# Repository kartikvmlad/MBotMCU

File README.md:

# Astra Robotics Controller (ARC-2040)

**A high-performance embedded control board designed for autonomous mobile robotics.**

The **Astra Robotics Controller** bridges the gap between prototyping boards and industrial PLCs. Built around the Raspberry Pi **RP2040** microcontroller, it integrates high-current motor drivers, redundant sensing, and non-volatile "Black Box" data logging into a unified, vibration-resistant PCB.

-> To view the schematic, download the repository and open the file **MBot.kicad_sch** in KiCad 

---

## 📋 Table of Contents
- [System Architecture](#-system-architecture)
- [Technical Specifications](#-technical-specifications)
- [Pin Configuration](#-pin-configuration)
- [Power System & Safety](#-power-system--safety)
- [Fabrication Notes](#-fabrication-notes-bom-criticals)
- [Getting Started](#-getting-started)

---

## 🏗 System Architecture

The board is divided into four isolated subsystems to minimize noise and maximize reliability:

1.  **Core Logic:** RP2040 Dual-Core Cortex-M0+ running at 133MHz with 2MB QSPI Flash.
2.  **Actuation:** Dual **DRV8876** H-Bridge drivers capable of 5A peak current, featuring hardware current regulation and fault feedback.
3.  **Sensing:**
    * **Motion:** InvenSense **MPU-9150** (9-DoF IMU) for heading and stabilization.
    * **Environment:** Bosch **BMP280** for barometric altitude and temperature.
    * **Data Logging:** Cypress **FM24W256 F-RAM** for high-speed, infinite-endurance telemetry logging.
4.  **Power:** A hybrid 12V $\to$ 6.5V $\to$ 5V/3.3V power tree using a high-efficiency **XL4015** Buck Converter.

---

## ⚙ Technical Specifications

| Feature | Specification |
| :--- | :--- |
| **Microcontroller** | Raspberry Pi RP2040 (Dual Core ARM M0+ @ 133MHz) |
| **Input Voltage** | 10V - 14V DC (Optimized for 3S LiPo or 12V Lead Acid) |
| **Motor Drive Output** | 2x Channels, 6.5V Regulated @ 3A Continuous / 5A Peak |
| **Logic Voltage** | 3.3V (System) / 5.0V (Auxiliary) |
| **IMU** | MPU-9150 (Gyro + Accel + Mag) via I2C `0x68` |
| **Altimeter** | BMP280 via I2C `0x76` |
| **Non-Volatile Memory** | 256 Kbit (32KB) Ferroelectric RAM via I2C `0x50` |
| **Expansion** | 4x ADC, 2x UART, 1x I2C, 1x SPI |

---

## 📍 Pin Configuration

### External Interfaces
| Port Label | Function | Pinout | Voltage Level |
| :--- | :--- | :--- | :--- |
| **J1 (SWD)** | Firmware Debugging | SWDIO, SWCLK, GND | 3.3V |
| **J3 (ADC)** | Analog Sensors | ADC0-2, 3V3, AGND | 3.3V |
| **J7 (UART0)** | GPS / Lidar | TX, RX, 3V3, GND | 3.3V |
| **J8 (I2C)** | Expansion / OLED | SDA, SCL, 3V3, GND | 3.3V |
| **J14 (PWM)** | Servo / GPIO | PWM_A, PWM_B, 3V3, GND | 3.3V |

### Onboard Switch Multiplexer
The board features hardware toggle switches to route the RP2040 ADC lines:
* **Position A (Left):** ADC monitors **Motor Current** (via DRV8876 IPROPI).
* **Position B (Right):** ADC monitors **External Sensors** (via Port J3).

---

## ⚡ Power System & Safety

This board implements a **Split-Rail Architecture**:
* **VMOT (6.5V Rail):** Powered by an XL4015 Buck Converter. Dedicated to Motors and High-Torque Servos.
* **VSYS (5.0V Rail):** Powered by an AMS1117-5.0. Dedicated to logic-level conversion.
* **3V3 (Logic Rail):** Powered by onboard LDO for MCU and Sensors.

**Safety Features:**
* **Reverse Polarity Protection:** 5A Schottky Diodes on input.
* **Over-Current Protection:** On-board Fuse (F1) and software-readable Current Sense.
* **Thermal Protection:** DRV8876 drivers have automatic thermal shutdown with LED indication (`nFAULT`).

> **⚠️ Usage Warning:** Port `J8`, `J9`, and `J10` (Motor/Aux) supply **6.5V** on Pin 3. Do not connect standard 5V-intolerant logic devices to this pin without checking datasheets.

---

## 🛠 Fabrication Notes (BOM Criticals)

If fabricating this board from the provided Gerbers, strictly adhere to the following component requirements to ensure power stability:

1.  **Diodes (D4, D5, D6):** MUST be **SS54** (5 Amp) or **MBRD1045** (10 Amp). Using SS34 (3A) may result in thermal failure under load.
2.  **Inductor (L1):** Footprint requires a **Shielded Power Inductor** (e.g., CDRH127) rated for **Isat > 5A**.
3.  **Capacitors:**
    * **Cout1:** 330µF/25V Electrolytic Low-ESR is mandatory for 6.5V rail stability.

---

## 🚀 Getting Started

1.  **Hardware Setup:**
    * Connect a 12V battery to the Screw Terminal (J3) or Barrel Jack (J2).
    * Connect motors to the JST outputs `M0` and `M1`.
2.  **Firmware Upload:**
    * Hold the **BOOT** button (or short `BOOTSEL` jumper).
    * Connect USB-C to a PC.
    * Copy your `.uf2` file to the `RPI-RP2` drive.
3.  **Software Addresses:**
    * `BMP280`: **0x76**
    * `MPU9150`: **0x68**
    * `FRAM`: **0x50**

---

**Project Lead:** Kartik Lad  
**Organization:** Astra Robotics  
**License:** Open Source Hardware

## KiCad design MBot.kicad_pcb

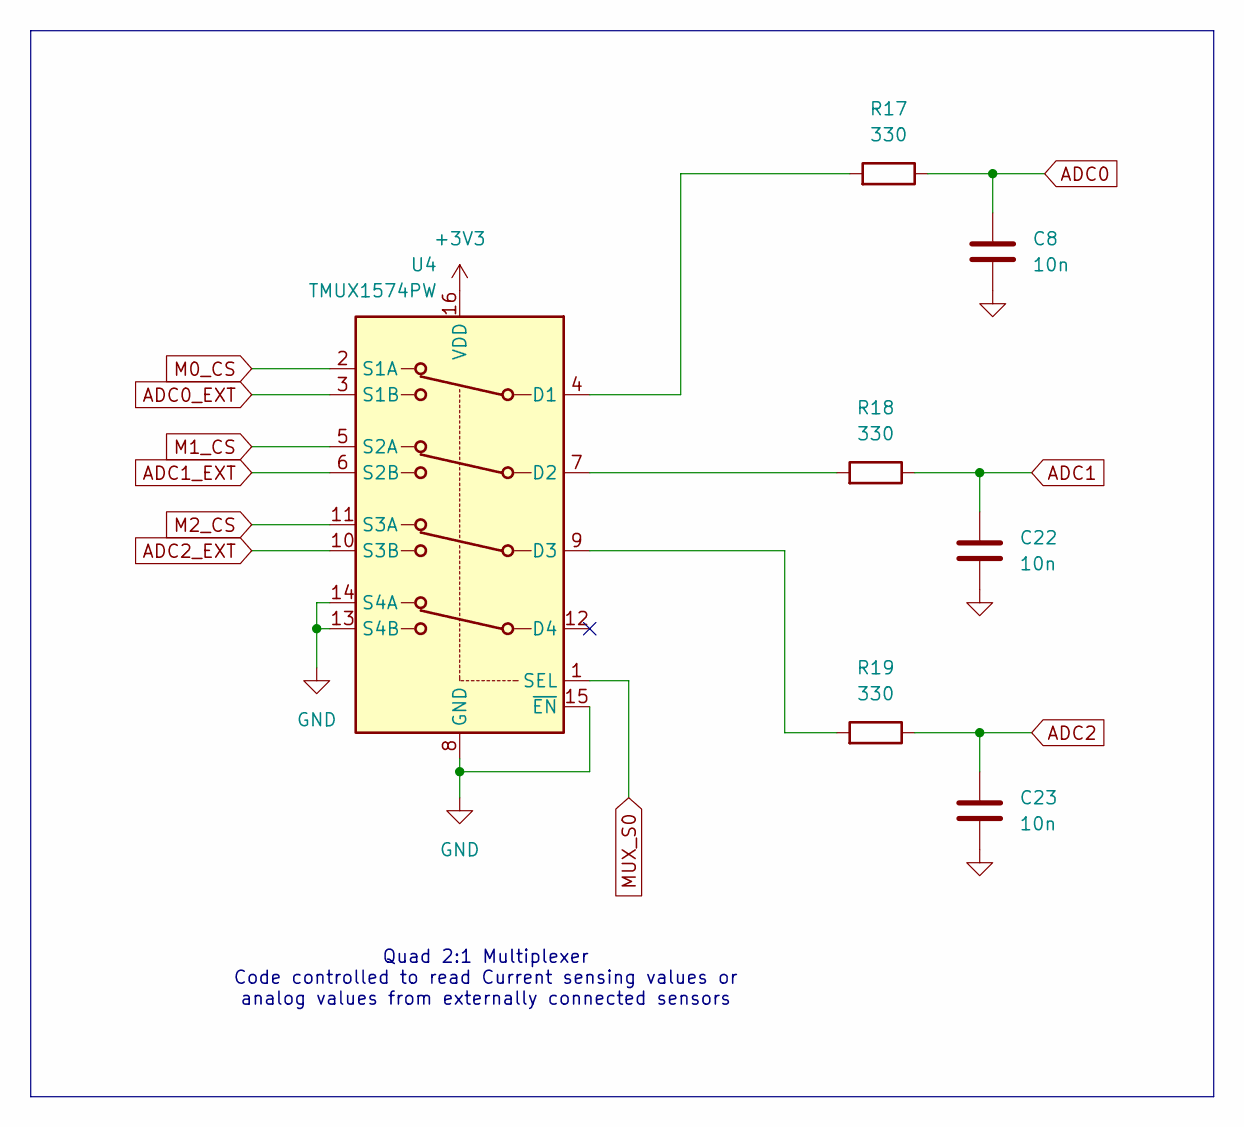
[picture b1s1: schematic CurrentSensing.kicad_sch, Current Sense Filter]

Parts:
C8, C22, C23: 10n; C_0603_1608Metric_Pad1.08x0.95mm_HandSolder
R17, R18, R19: 330; R_0603_1608Metric_Pad0.98x0.95mm_HandSolder
U4: TMUX1574PW; TSSOP-16_4.4x5mm_P0.65mm

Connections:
+3V3: U4.16 (VDD); also elsewhere on the board
ADC0: C8.1, R17.1; also elsewhere on the board
ADC0_EXT: U4.3 (S1B); also elsewhere on the board
ADC1: C22.1, R18.1; also elsewhere on the board
ADC1_EXT: U4.6 (S2B); also elsewhere on the board
ADC2: C23.1, R19.1; also elsewhere on the board
ADC2_EXT: U4.10 (S3B); also elsewhere on the board
GND: C8.2, C22.2, C23.2, U4.8 (GND), U4.13 (S4B), U4.14 (S4A), U4.15 (~EN); also elsewhere on the board
M0_CS: U4.2 (S1A); also elsewhere on the board
M1_CS: U4.5 (S2A); also elsewhere on the board
M2_CS: U4.11 (S3A); also elsewhere on the board
MUX_S0: U4.1 (SEL); also elsewhere on the board
unnamed: R17.2, U4.4 (D1)
unnamed: R18.2, U4.7 (D2)
unnamed: R19.2, U4.9 (D3)

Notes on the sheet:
Quad 2:1 Multiplexer Code controlled to read Current sensing values or analog values from externally connected sensors

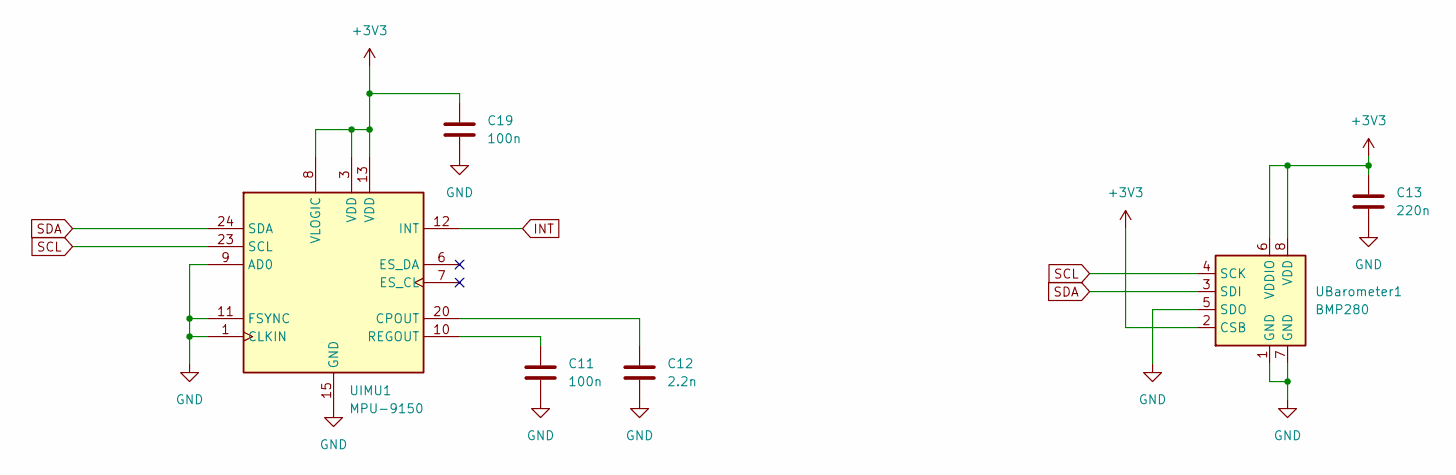
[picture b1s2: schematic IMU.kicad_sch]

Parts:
C11, C19: 100n; C_0603_1608Metric_Pad1.08x0.95mm_HandSolder
C12: 2.2n; C_0603_1608Metric_Pad1.08x0.95mm_HandSolder
C13: 220n; C_0603_1608Metric_Pad1.08x0.95mm_HandSolder
UBarometer1: BMP280; Bosch_LGA-8_2x2.5mm_P0.65mm_ClockwisePinNumbering
UIMU1: MPU-9150; InvenSense_QFN-24_4x4mm_P0.5mm

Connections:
+3V3: C13.1, C19.1, UBarometer1.2 (CSB), UBarometer1.6 (VDDIO), UBarometer1.8 (VDD), UIMU1.3 (VDD), UIMU1.8 (VLOGIC), UIMU1.13 (VDD); also elsewhere on the board
GND: C11.2, C12.2, C13.2, C19.2, UBarometer1.1 (GND), UBarometer1.5 (SDO), UBarometer1.7 (GND), UIMU1.1 (CLKIN), UIMU1.9 (AD0), UIMU1.11 (FSYNC), UIMU1.15 (GND), UIMU1.17 (GND), UIMU1.18 (GND); also elsewhere on the board
INT: UIMU1.12 (INT); also elsewhere on the board
unnamed: C12.1, UIMU1.20 (CPOUT)
unnamed: C11.1, UIMU1.10 (REGOUT)
SCL: UBarometer1.4 (SCK), UIMU1.23 (SCL); also elsewhere on the board
SDA: UBarometer1.3 (SDI), UIMU1.24 (SDA); also elsewhere on the board

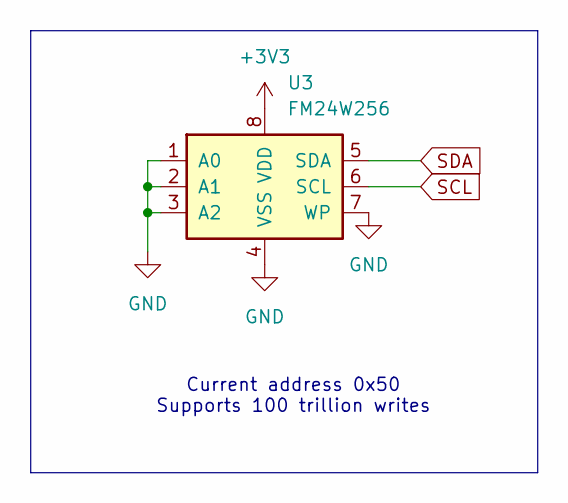
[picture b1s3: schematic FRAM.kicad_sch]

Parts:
U3: FM24W256; SOIC-8_3.9x4.9mm_P1.27mm

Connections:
+3V3: U3.8 (VDD); also elsewhere on the board
GND: U3.1 (A0), U3.2 (A1), U3.3 (A2), U3.4 (VSS), U3.7 (WP); also elsewhere on the board
SCL: U3.6 (SCL); also elsewhere on the board
SDA: U3.5 (SDA); also elsewhere on the board

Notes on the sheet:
Current address 0x50 Supports 100 trillion writes

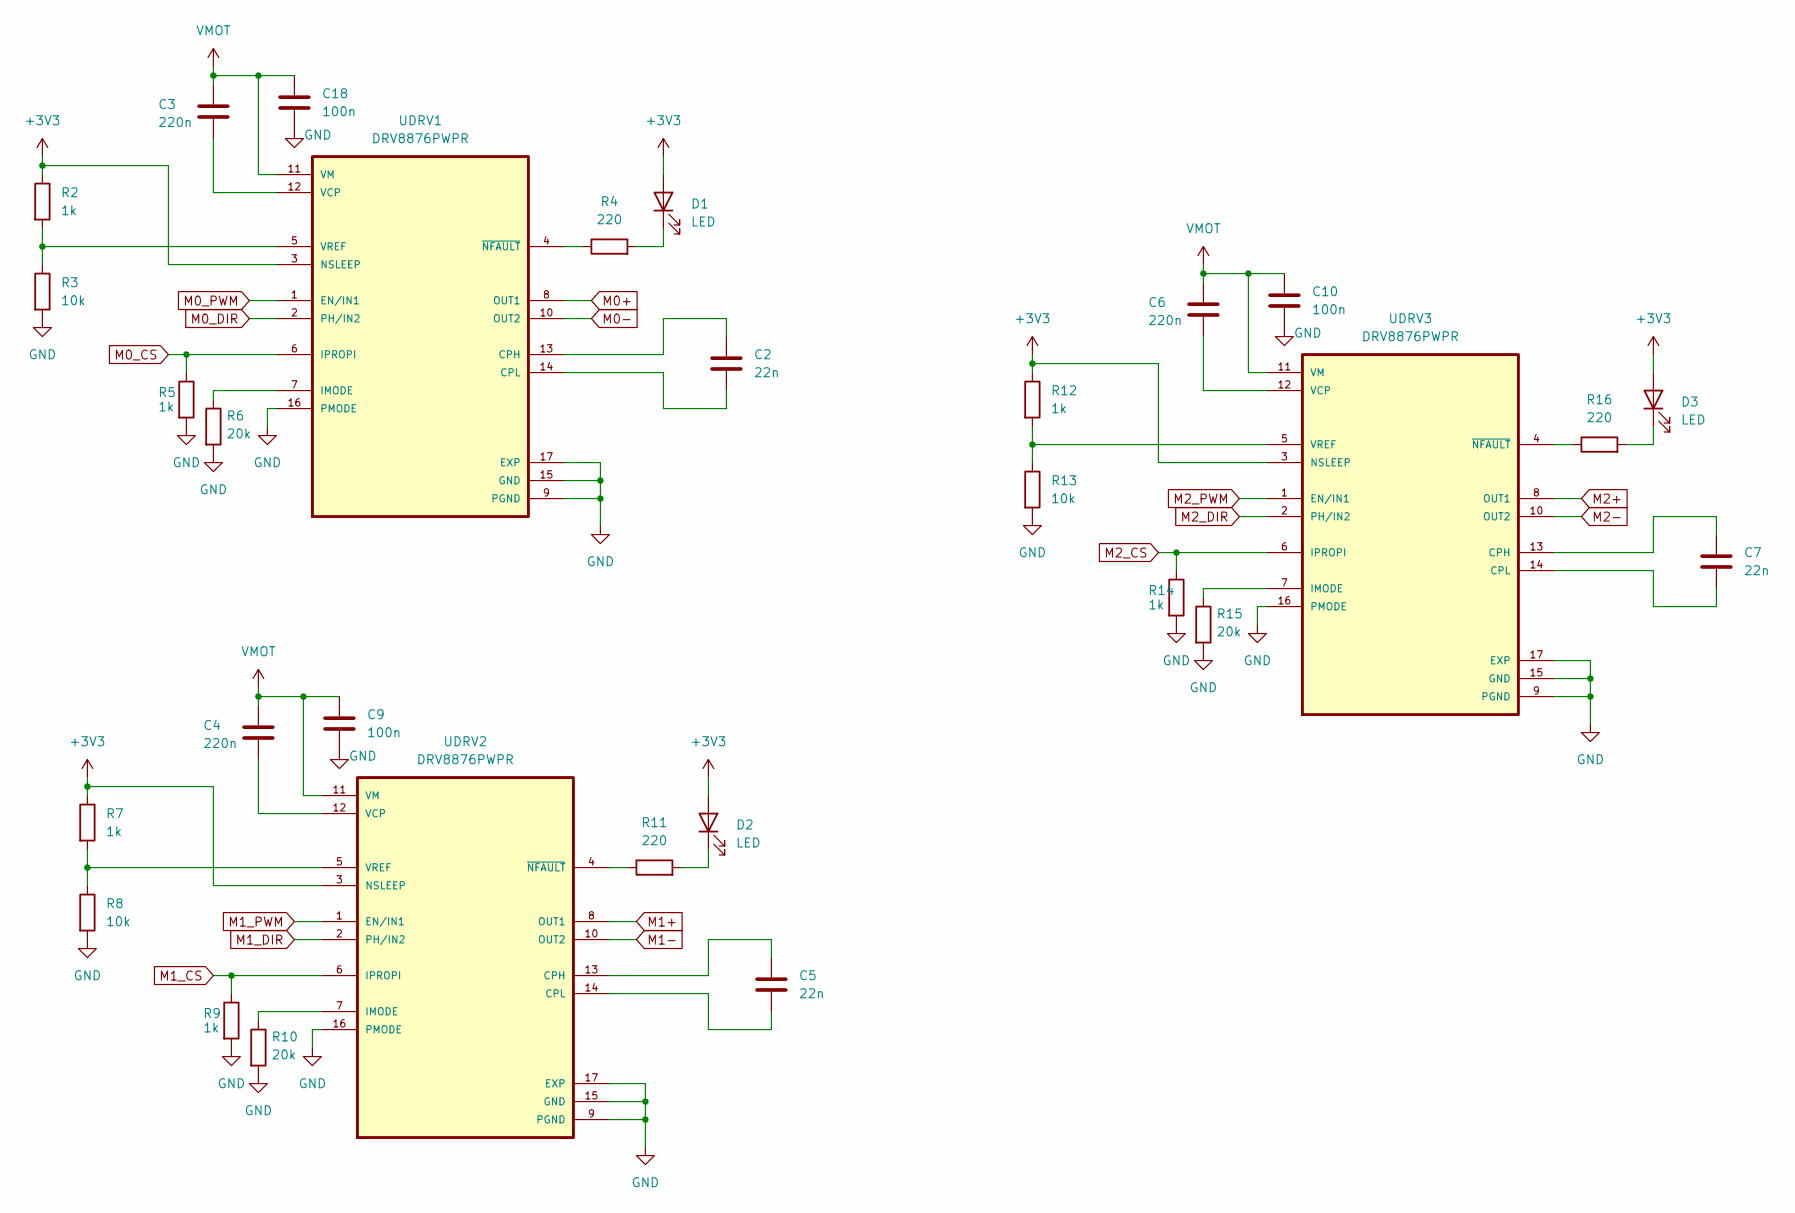
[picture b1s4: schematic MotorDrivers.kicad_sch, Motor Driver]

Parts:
C2, C5, C7: 22n; C_0603_1608Metric_Pad1.08x0.95mm_HandSolder
C3, C4, C6: 220n; C_0603_1608Metric_Pad1.08x0.95mm_HandSolder
C9, C10, C18: 100n; C_0603_1608Metric_Pad1.08x0.95mm_HandSolder
D1, D2, D3: LED; LED_0805_2012Metric_Pad1.15x1.40mm_HandSolder
R2, R5, R7, R9, R12, R14: 1k; R_0603_1608Metric_Pad0.98x0.95mm_HandSolder
R3, R8, R13: 10k; R_0603_1608Metric_Pad0.98x0.95mm_HandSolder
R4, R11, R16: 220; R_0603_1608Metric_Pad0.98x0.95mm_HandSolder
R6, R10, R15: 20k; R_0603_1608Metric_Pad0.98x0.95mm_HandSolder
UDRV1, UDRV2, UDRV3: DRV8876PWPR; IC_DRV8876PWPR; PARTREV E

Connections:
+3V3: D1.2 (A), D2.2 (A), D3.2 (A), R2.1, R7.1, R12.1, UDRV1.3 (NSLEEP), UDRV2.3 (NSLEEP), UDRV3.3 (NSLEEP); also elsewhere on the board
GND: C9.2, C10.2, C18.2, R3.2, R5.2, R6.2, R8.2, R9.2, R10.2, R13.2, R14.2, R15.2, UDRV1.9 (PGND), UDRV1.15 (GND), UDRV1.16 (PMODE), UDRV1.17 (EXP), UDRV2.9 (PGND), UDRV2.15 (GND), UDRV2.16 (PMODE), UDRV2.17 (EXP), UDRV3.9 (PGND), UDRV3.15 (GND), UDRV3.16 (PMODE), UDRV3.17 (EXP); also elsewhere on the board
M0+: UDRV1.8 (OUT1); also elsewhere on the board
M0-: UDRV1.10 (OUT2); also elsewhere on the board
M0_CS: R5.1, UDRV1.6 (IPROPI); also elsewhere on the board
M0_DIR: UDRV1.2 (PH/IN2); also elsewhere on the board
M0_PWM: UDRV1.1 (EN/IN1); also elsewhere on the board
M1+: UDRV2.8 (OUT1); also elsewhere on the board
M1-: UDRV2.10 (OUT2); also elsewhere on the board
M1_CS: R9.1, UDRV2.6 (IPROPI); also elsewhere on the board
M1_DIR: UDRV2.2 (PH/IN2); also elsewhere on the board
M1_PWM: UDRV2.1 (EN/IN1); also elsewhere on the board
M2+: UDRV3.8 (OUT1); also elsewhere on the board
M2-: UDRV3.10 (OUT2); also elsewhere on the board
M2_CS: R14.1, UDRV3.6 (IPROPI); also elsewhere on the board
M2_DIR: UDRV3.2 (PH/IN2); also elsewhere on the board
M2_PWM: UDRV3.1 (EN/IN1); also elsewhere on the board
unnamed: D1.1 (K), R4.2
unnamed: D2.1 (K), R11.2
unnamed: D3.1 (K), R16.2
unnamed: C2.1, UDRV1.13 (CPH)
unnamed: C2.2, UDRV1.14 (CPL)
unnamed: R6.1, UDRV1.7 (IMODE)
unnamed: C3.2, UDRV1.12 (VCP)
unnamed: R2.2, R3.1, UDRV1.5 (VREF)
unnamed: R4.1, UDRV1.4 (~NFAULT)
unnamed: C5.1, UDRV2.13 (CPH)
unnamed: C5.2, UDRV2.14 (CPL)
unnamed: R10.1, UDRV2.7 (IMODE)
unnamed: C4.2, UDRV2.12 (VCP)
unnamed: R7.2, R8.1, UDRV2.5 (VREF)
unnamed: R11.1, UDRV2.4 (~NFAULT)
unnamed: C7.1, UDRV3.13 (CPH)
unnamed: C7.2, UDRV3.14 (CPL)
unnamed: R15.1, UDRV3.7 (IMODE)
unnamed: C6.2, UDRV3.12 (VCP)
unnamed: R12.2, R13.1, UDRV3.5 (VREF)
unnamed: R16.1, UDRV3.4 (~NFAULT)
VMOT: C3.1, C4.1, C6.1, C9.1, C10.1, C18.1, UDRV1.11 (VM), UDRV2.11 (VM), UDRV3.11 (VM); also elsewhere on the board

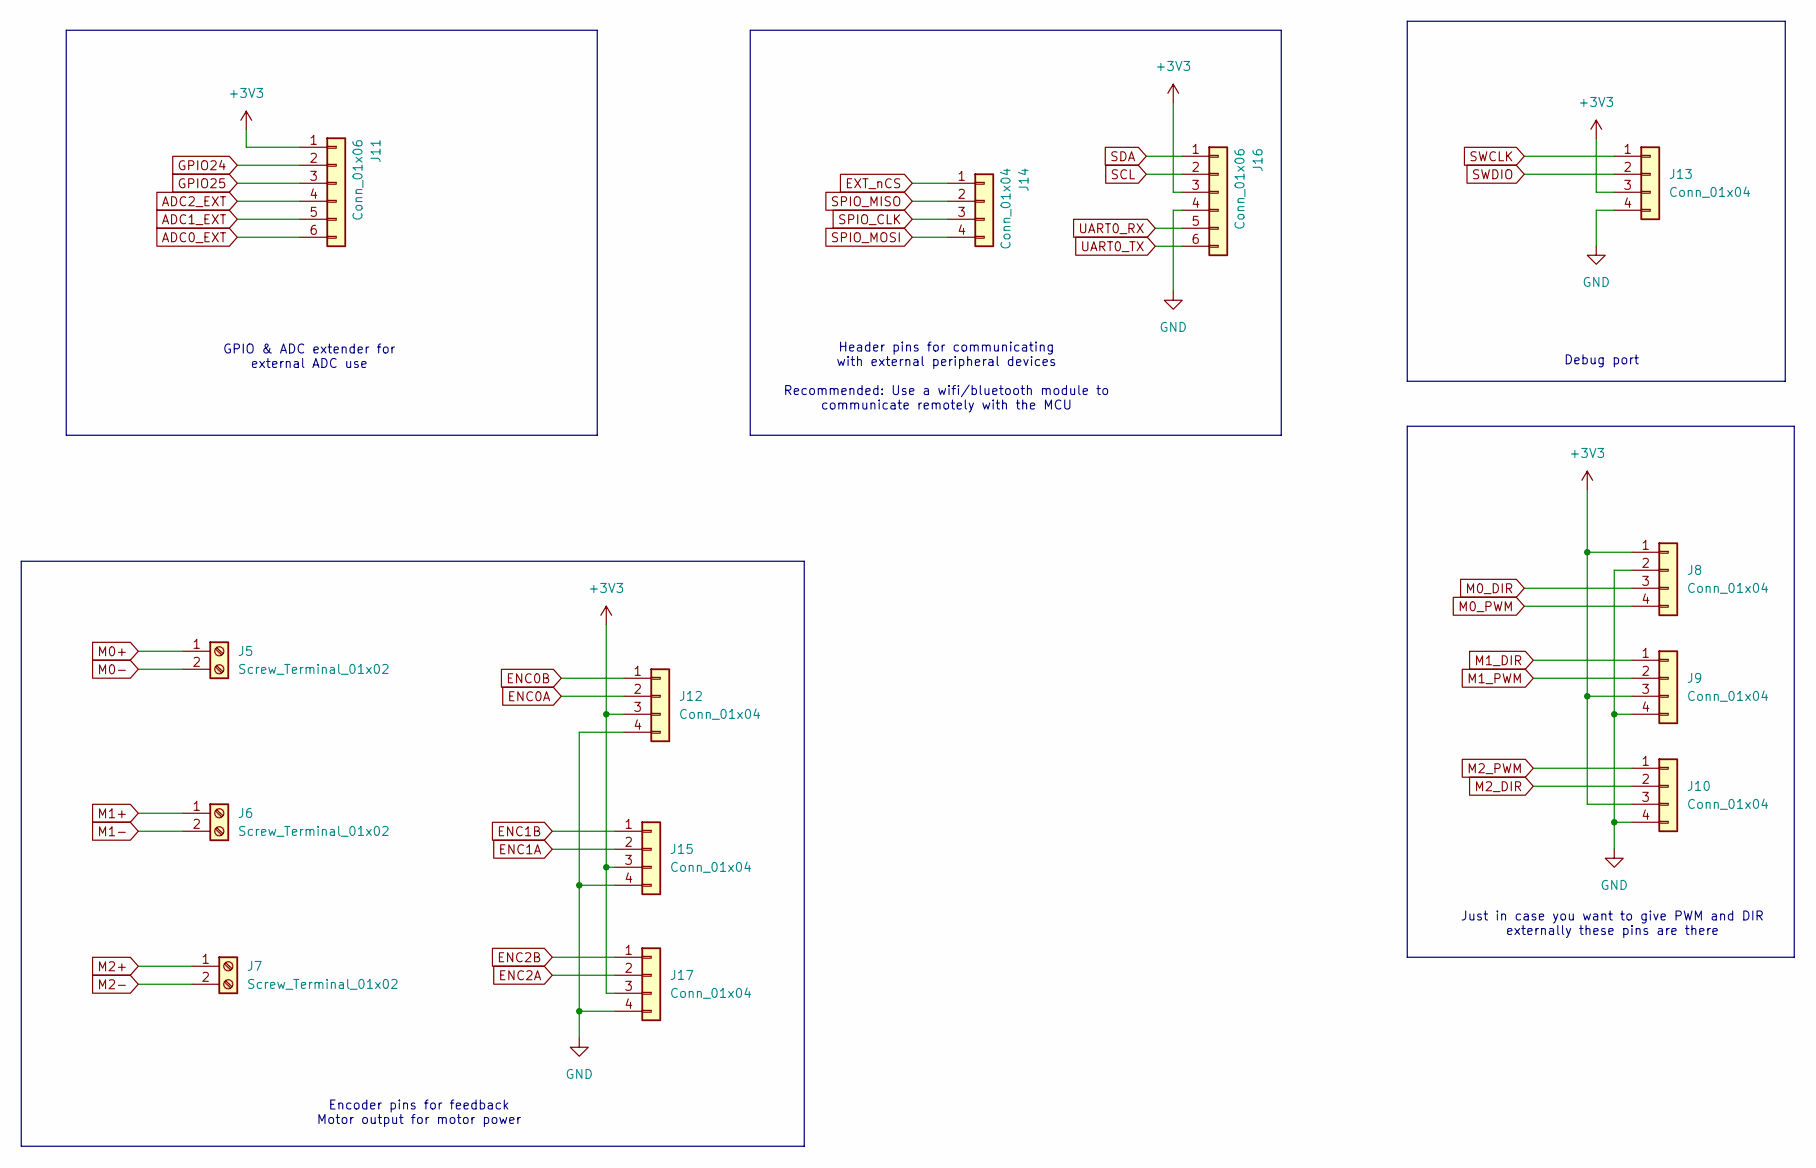
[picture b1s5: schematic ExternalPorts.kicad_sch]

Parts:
J5, J6, J7: Screw_Terminal_01x02; TerminalBlock_Phoenix_MPT-0,5-2-2.54_1x02_P2.54mm_Horizontal
J8, J9, J10, J12, J13, J14, J15, J17: Conn_01x04; JST_ZH_B4B-ZR_1x04_P1.50mm_Vertical
J11, J16: Conn_01x06; JST_ZH_B6B-ZR_1x06_P1.50mm_Vertical

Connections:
+3V3: J8.1, J9.3, J10.3, J11.1, J12.3, J13.3, J15.3, J16.3, J17.3; also elsewhere on the board
ADC0_EXT: J11.6; also elsewhere on the board
ADC1_EXT: J11.5; also elsewhere on the board
ADC2_EXT: J11.4; also elsewhere on the board
ENC0A: J12.2; also elsewhere on the board
ENC0B: J12.1; also elsewhere on the board
ENC1A: J15.2; also elsewhere on the board
ENC1B: J15.1; also elsewhere on the board
ENC2A: J17.2; also elsewhere on the board
ENC2B: J17.1; also elsewhere on the board
EXT_nCS: J14.1; also elsewhere on the board
GND: J8.2, J9.4, J10.4, J12.4, J13.4, J15.4, J16.4, J17.4; also elsewhere on the board
GPIO24: J11.2; also elsewhere on the board
GPIO25: J11.3; also elsewhere on the board
M0+: J5.1; also elsewhere on the board
M0-: J5.2; also elsewhere on the board
M0_DIR: J8.3; also elsewhere on the board
M0_PWM: J8.4; also elsewhere on the board
M1+: J6.1; also elsewhere on the board
M1-: J6.2; also elsewhere on the board
M1_DIR: J9.1; also elsewhere on the board
M1_PWM: J9.2; also elsewhere on the board
M2+: J7.1; also elsewhere on the board
M2-: J7.2; also elsewhere on the board
M2_DIR: J10.2; also elsewhere on the board
M2_PWM: J10.1; also elsewhere on the board
SCL: J16.2; also elsewhere on the board
SDA: J16.1; also elsewhere on the board
SPIO_CLK: J14.3; also elsewhere on the board
SPIO_MISO: J14.2; also elsewhere on the board
SPIO_MOSI: J14.4; also elsewhere on the board
SWCLK: J13.1; also elsewhere on the board
SWDIO: J13.2; also elsewhere on the board
UART0_RX: J16.5; also elsewhere on the board
UART0_TX: J16.6; also elsewhere on the board

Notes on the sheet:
GPIO & ADC extender for external ADC use
Debug port
Just in case you want to give PWM and DIR externally these pins are there
Header pins for communicating with external peripheral devices Recommended: Use a wifi/bluetooth module to communicate remotely with the MCU
Encoder pins for feedback Motor output for motor power

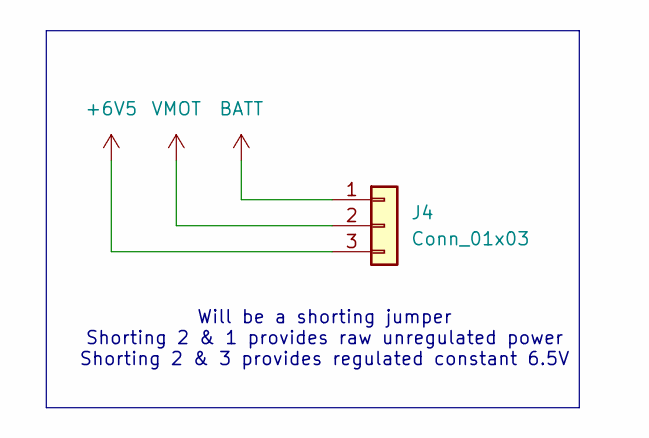
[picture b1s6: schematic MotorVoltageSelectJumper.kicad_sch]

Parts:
J4: Conn_01x03; JST_VH_B3P-VH_1x03_P3.96mm_Vertical

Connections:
+6V5: J4.3; also elsewhere on the board
BATT: J4.1; also elsewhere on the board
VMOT: J4.2; also elsewhere on the board

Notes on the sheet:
Will be a shorting jumper Shorting 2 & 1 provides raw unregulated power Shorting 2 & 3 provides regulated constant 6.5V

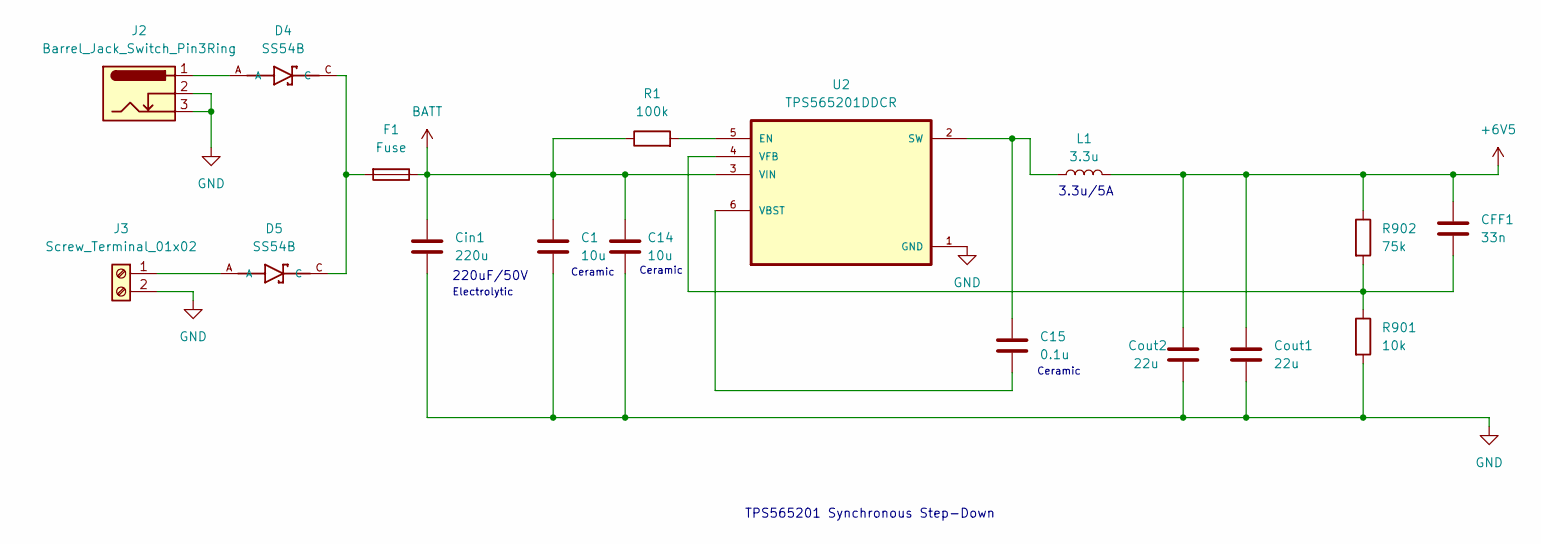
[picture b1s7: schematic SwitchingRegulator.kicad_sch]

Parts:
C1, C14: 10u; C_0805_2012Metric_Pad1.18x1.45mm_HandSolder
C15: 0.1u; C_0603_1608Metric_Pad1.08x0.95mm_HandSolder
CFF1: 33n; C_0603_1608Metric_Pad1.08x0.95mm_HandSolder
Cin1: 220u; C_0805_2012Metric_Pad1.18x1.45mm_HandSolder
Cout1, Cout2: 22u; C_0805_2012Metric_Pad1.18x1.45mm_HandSolder
D4, D5: SS54B; DIOM4336X244N
F1: Fuse; Fuse_Littelfuse-NANO2-451_453
J2: Barrel_Jack_Switch_Pin3Ring; BarrelJack_Horizontal
J3: Screw_Terminal_01x02; TerminalBlock_Phoenix_MPT-0,5-2-2.54_1x02_P2.54mm_Horizontal
L1: 3.3u; L_Bourns_SRP7028A_7.3x6.6mm
R1: 100k; R_0603_1608Metric_Pad0.98x0.95mm_HandSolder
R901: 10k; R_0603_1608Metric_Pad0.98x0.95mm_HandSolder
R902: 75k; R_0603_1608Metric_Pad0.98x0.95mm_HandSolder
U2: TPS565201DDCR; SOT95P280X110-6N

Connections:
+6V5: CFF1.1, Cout1.1, Cout2.1, L1.2, R902.1; also elsewhere on the board
BATT: C1.1, C14.1, Cin1.1, F1.1, R1.1, U2.3 (VIN); also elsewhere on the board
GND: C1.2, C14.2, Cin1.2, Cout1.2, Cout2.2, J2.2, J2.3, J3.2, R901.2, U2.1 (GND); also elsewhere on the board
unnamed: D4.A, J2.1
unnamed: D4.C, D5.C, F1.2
unnamed: D5.A, J3.1
unnamed: R1.2, U2.5 (EN)
unnamed: C15.1, L1.1, U2.2 (SW)
unnamed: C15.2, U2.6 (VBST)
unnamed: CFF1.2, R901.1, R902.2, U2.4 (VFB)

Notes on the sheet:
Ceramic
TPS565201 Synchronous Step-Down
220uF/50V
Electrolytic
3.3u/5A

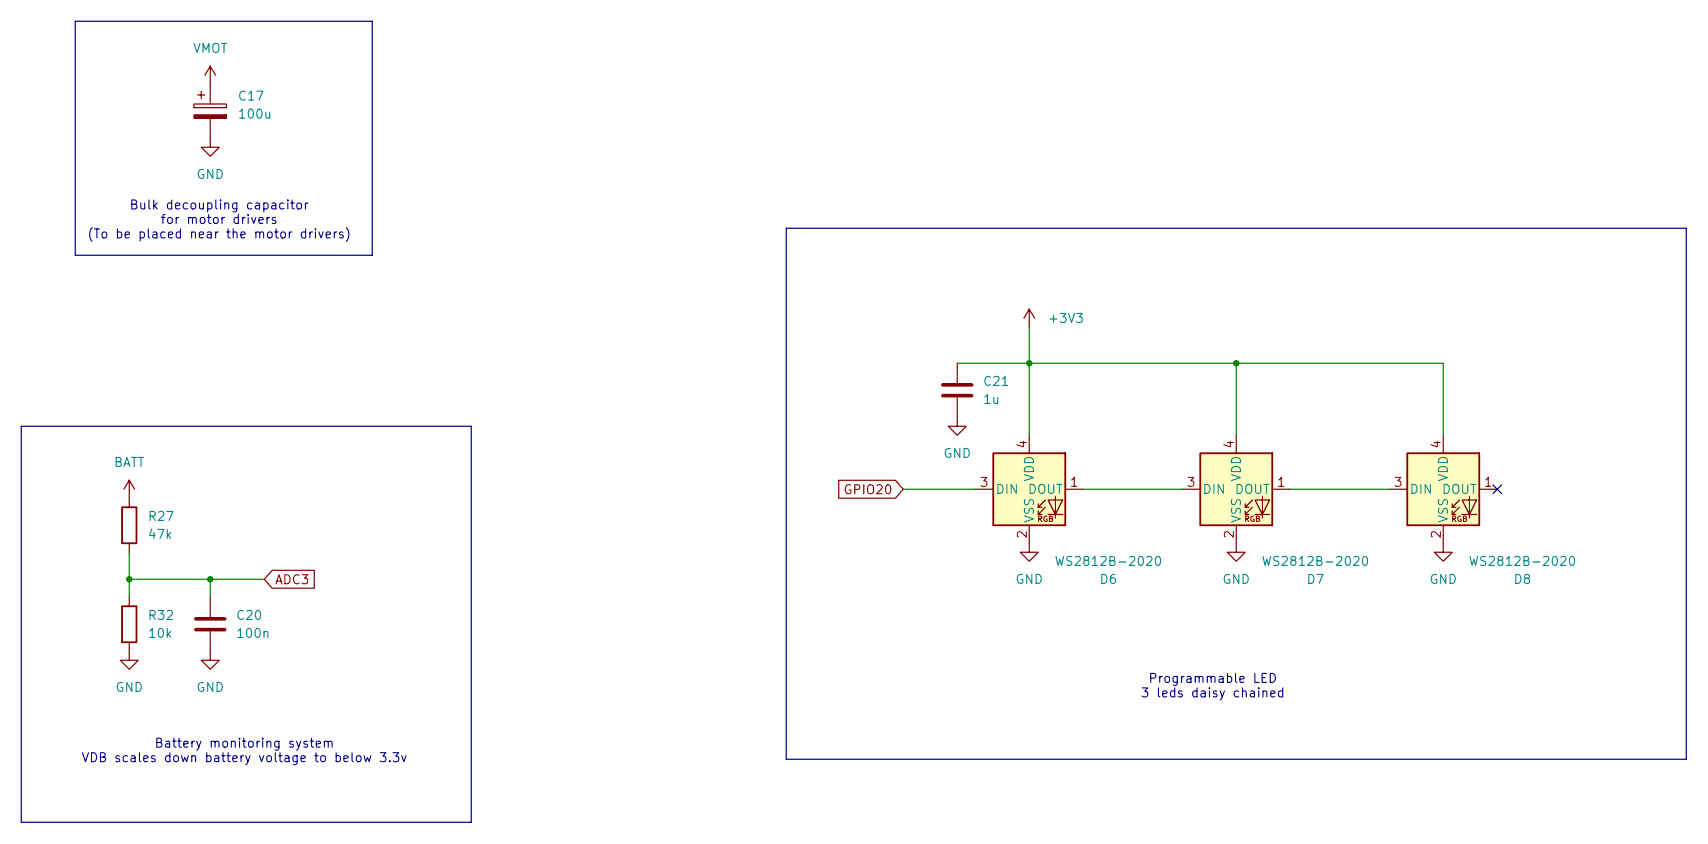
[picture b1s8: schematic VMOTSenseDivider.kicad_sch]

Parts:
C17: 100u; C_0805_2012Metric_Pad1.18x1.45mm_HandSolder
C20: 100n; C_0603_1608Metric_Pad1.08x0.95mm_HandSolder
C21: 1u; C_0603_1608Metric_Pad1.08x0.95mm_HandSolder
D6, D7, D8: WS2812B-2020; LED_WS2812B-2020_PLCC4_2.0x2.0mm
R27: 47k; R_0603_1608Metric_Pad0.98x0.95mm_HandSolder
R32: 10k; R_0603_1608Metric_Pad0.98x0.95mm_HandSolder

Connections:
+3V3: C21.1, D6.4 (VDD), D7.4 (VDD), D8.4 (VDD); also elsewhere on the board
ADC3: C20.1, R27.2, R32.1; also elsewhere on the board
BATT: R27.1; also elsewhere on the board
GND: C17.2, C20.2, C21.2, D6.2 (VSS), D7.2 (VSS), D8.2 (VSS), R32.2; also elsewhere on the board
GPIO20: D6.3 (DIN); also elsewhere on the board
unnamed: D6.1 (DOUT), D7.3 (DIN)
unnamed: D7.1 (DOUT), D8.3 (DIN)
VMOT: C17.1; also elsewhere on the board

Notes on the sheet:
Battery monitoring system VDB scales down battery voltage to below 3.3v
Bulk decoupling capacitor for motor drivers (To be placed near the motor drivers)
Programmable LED 3 leds daisy chained

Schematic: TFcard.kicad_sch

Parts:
J1: Micro_SD_Card_Det1; microSD_HC_Hirose_DM3AT-SF-PEJM5
U1: 74AUC1G19; SOT-23-6_Handsoldering

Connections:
+3V3: J1.4 (VDD), U1.5 (VCC); also elsewhere on the board
EXT_nCS: U1.6 (Y0); also elsewhere on the board
EXT/SD: U1.1 (A); also elsewhere on the board
GND: J1.6 (VSS), J1.10 (SHIELD), U1.2 (GND); also elsewhere on the board
SD_nCS: J1.2 (DAT3/CD), U1.4 (Y1)
SPIO_CLK: J1.5 (CLK); also elsewhere on the board
SPIO_CS: U1.3 (~E); also elsewhere on the board
SPIO_MISO: J1.7 (DAT0); also elsewhere on the board
SPIO_MOSI: J1.3 (CMD); also elsewhere on the board

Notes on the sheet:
DET is for physical detection of card

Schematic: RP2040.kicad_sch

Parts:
C16, C105, C106, C107, C109, C110, C111, C112, C113, C114, C115, C120: 100n; C_0603_1608Metric_Pad1.08x0.95mm_HandSolder
C101, C104, C117: 10u; C_0805_2012Metric_Pad1.18x1.45mm_HandSolder
C102, C103: 15p; C_0603_1608Metric_Pad1.08x0.95mm_HandSolder
C108: 1u; C_0603_1608Metric_Pad1.08x0.95mm_HandSolder
D101, D102: SS14; D_SMA_Handsoldering
FB1: FerriteBead; L_0805_2012Metric_Pad1.05x1.20mm_HandSolder
JUSBC1: USB_C_Receptacle_USB2.0_16P; USB_C_Receptacle_GCT_USB4085
R23, R24: 4.7k; R_0603_1608Metric_Pad0.98x0.95mm_HandSolder
R101, R105: 1k; R_0603_1608Metric_Pad0.98x0.95mm_HandSolder
R109: 5.1k; R_0603_1608Metric_Pad0.98x0.95mm_HandSolder
RDminus1: 27; R_0603_1608Metric_Pad0.98x0.95mm_HandSolder
RDplus1: 27; R_0603_1608Metric_Pad0.98x0.95mm_HandSolder
RUSB1: 5.1k; R_0603_1608Metric_Pad0.98x0.95mm_HandSolder
SW4: SW_SPST; SW_Push_SPST_NO_Alps_SKRK
SWRESET1: SW_SPST; SW_Push_SPST_NO_Alps_SKRK
UESD1: USBLC6-2SC6; SOT-23-6
UFlashMem1: W25Q16JVSS; SOIC-8_5.3x5.3mm_P1.27mm
ULDO1: NCP1117-3.3_SOT223; SOT-223-3_TabPin2
URP2040: RP2040; QFN-56-1EP_7x7mm_P0.4mm_EP3.2x3.2mm
YCrystalOscillator1: ABM8-272-T3; XTAL_ABM8-272-T3; PARTREV 07-29-20

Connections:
+1V1: C106.1, C107.1, C108.1, URP2040.23 (DVDD), URP2040.45 (VREG_VOUT), URP2040.50 (DVDD)
+3V3: C16.1, C104.1, C105.1, C109.1, C110.1, C111.1, C112.1, C113.1, C114.1, C115.1, C117.1, FB1.1, R23.1, R24.1, UFlashMem1.8 (VCC), ULDO1.3 (VI), URP2040.1 (IOVDD), URP2040.10 (IOVDD), URP2040.22 (IOVDD), URP2040.33 (IOVDD), URP2040.42 (IOVDD), URP2040.44 (VREG_IN), URP2040.48 (USB_VDD), URP2040.49 (IOVDD); also elsewhere on the board
+6V5: D101.2 (A); also elsewhere on the board
/RP2040/QSPI_SCLK: UFlashMem1.6 (CLK), URP2040.53 (QSPI_SD0)
/RP2040/QSPI_SD0: UFlashMem1.5 (DI/IO_{0}), URP2040.55 (QSPI_SD1)
/RP2040/QSPI_SD1: UFlashMem1.2 (DO/IO_{1}), URP2040.54 (QSPI_SD2)
/RP2040/QSPI_SD2: UFlashMem1.3 (~WP/IO_{2}), URP2040.51 (QSPI_SD3)
/RP2040/QSPI_SD3: UFlashMem1.7 (~HOLD/~RESET/IO_{3}), URP2040.52 (QSPI_SCLK)
/RP2040/QSPI_SS: R101.2, UFlashMem1.1 (~CS), URP2040.56 (QSPI_SS)
/RP2040/USB_D1+: RDplus1.1, UESD1.6 (I/O1)
/RP2040/USB_D1-: RDminus1.1, UESD1.4 (I/O2)
/RP2040/USB_D2+: RDplus1.2, URP2040.47 (USB_DP)
/RP2040/USB_D2-: RDminus1.2, URP2040.46 (USB_DM)
/RP2040/USB_D+: JUSBC1.A6 (D+), JUSBC1.B6 (D+), UESD1.1 (I/O1)
/RP2040/USB_D-: JUSBC1.A7 (D-), JUSBC1.B7 (D-), UESD1.3 (I/O2)
/RP2040/XIN: C102.2, URP2040.20 (XIN), YCrystalOscillator1.1
/RP2040/XOUT: R105.2, URP2040.21 (XOUT)
ADC0: URP2040.38 (GPIO26_ADC0); also elsewhere on the board
ADC1: URP2040.39 (GPIO27_ADC1); also elsewhere on the board
ADC2: URP2040.40 (GPIO28_ADC2); also elsewhere on the board
ADC3: URP2040.41 (GPIO29_ADC3); also elsewhere on the board
ENC0A: URP2040.8 (GPIO6); also elsewhere on the board
ENC0B: URP2040.9 (GPIO7); also elsewhere on the board
ENC1A: URP2040.11 (GPIO8); also elsewhere on the board
ENC1B: URP2040.12 (GPIO9); also elsewhere on the board
ENC2A: URP2040.13 (GPIO10); also elsewhere on the board
ENC2B: URP2040.14 (GPIO11); also elsewhere on the board
EXT/SD: URP2040.32 (GPIO21); also elsewhere on the board
GND: C16.2, C101.2, C102.1, C103.1, C104.2, C105.2, C106.2, C107.2, C108.2, C109.2, C110.2, C111.2, C112.2, C113.2, C114.2, C115.2, C117.2, C120.1, JUSBC1.A1 (GND), JUSBC1.A12 (GND), JUSBC1.B1 (GND), JUSBC1.B12 (GND), JUSBC1.S1 (SHIELD), R109.2, RUSB1.2, SW4.1 (A), SWRESET1.2 (B), UESD1.2 (GND), UFlashMem1.4 (GND), ULDO1.1 (GND), URP2040.19 (TESTEN), URP2040.57 (GND), YCrystalOscillator1.2 (GND), YCrystalOscillator1.4 (GND); also elsewhere on the board
GPIO20: URP2040.31 (GPIO20); also elsewhere on the board
GPIO24: URP2040.36 (GPIO24); also elsewhere on the board
GPIO25: URP2040.37 (GPIO25); also elsewhere on the board
INT: URP2040.34 (GPIO22); also elsewhere on the board
M0_DIR: URP2040.17 (GPIO14); also elsewhere on the board
M0_PWM: URP2040.4 (GPIO2); also elsewhere on the board
M1_DIR: URP2040.18 (GPIO15); also elsewhere on the board
M1_PWM: URP2040.5 (GPIO3); also elsewhere on the board
M2_DIR: URP2040.16 (GPIO13); also elsewhere on the board
M2_PWM: URP2040.15 (GPIO12); also elsewhere on the board
MUX_S0: URP2040.35 (GPIO23); also elsewhere on the board
unnamed: C103.2, R105.1, YCrystalOscillator1.3
unnamed: C101.1, D101.1 (K), D102.1 (K), ULDO1.2 (VO)
unnamed: JUSBC1.A5 (CC1), RUSB1.1
unnamed: JUSBC1.B5 (CC2), R109.1
unnamed: R101.1, SW4.2 (B)
unnamed: C120.2, FB1.2, URP2040.43 (ADC_AVDD)
RUN: SWRESET1.1 (A), URP2040.26 (RUN)
SCL: R23.2, URP2040.7 (GPIO5); also elsewhere on the board
SDA: R24.2, URP2040.6 (GPIO4); also elsewhere on the board
SPIO_CLK: URP2040.29 (GPIO18); also elsewhere on the board
SPIO_CS: URP2040.28 (GPIO17); also elsewhere on the board
SPIO_MISO: URP2040.27 (GPIO16); also elsewhere on the board
SPIO_MOSI: URP2040.30 (GPIO19); also elsewhere on the board
SWCLK: URP2040.24 (SWCLK); also elsewhere on the board
SWDIO: URP2040.25 (SWD); also elsewhere on the board
UART0_RX: URP2040.2 (GPIO0); also elsewhere on the board
UART0_TX: URP2040.3 (GPIO1); also elsewhere on the board
VBUS: D102.2 (A), JUSBC1.A4 (VBUS), JUSBC1.A9 (VBUS), JUSBC1.B4 (VBUS), JUSBC1.B9 (VBUS), UESD1.5 (VBUS)

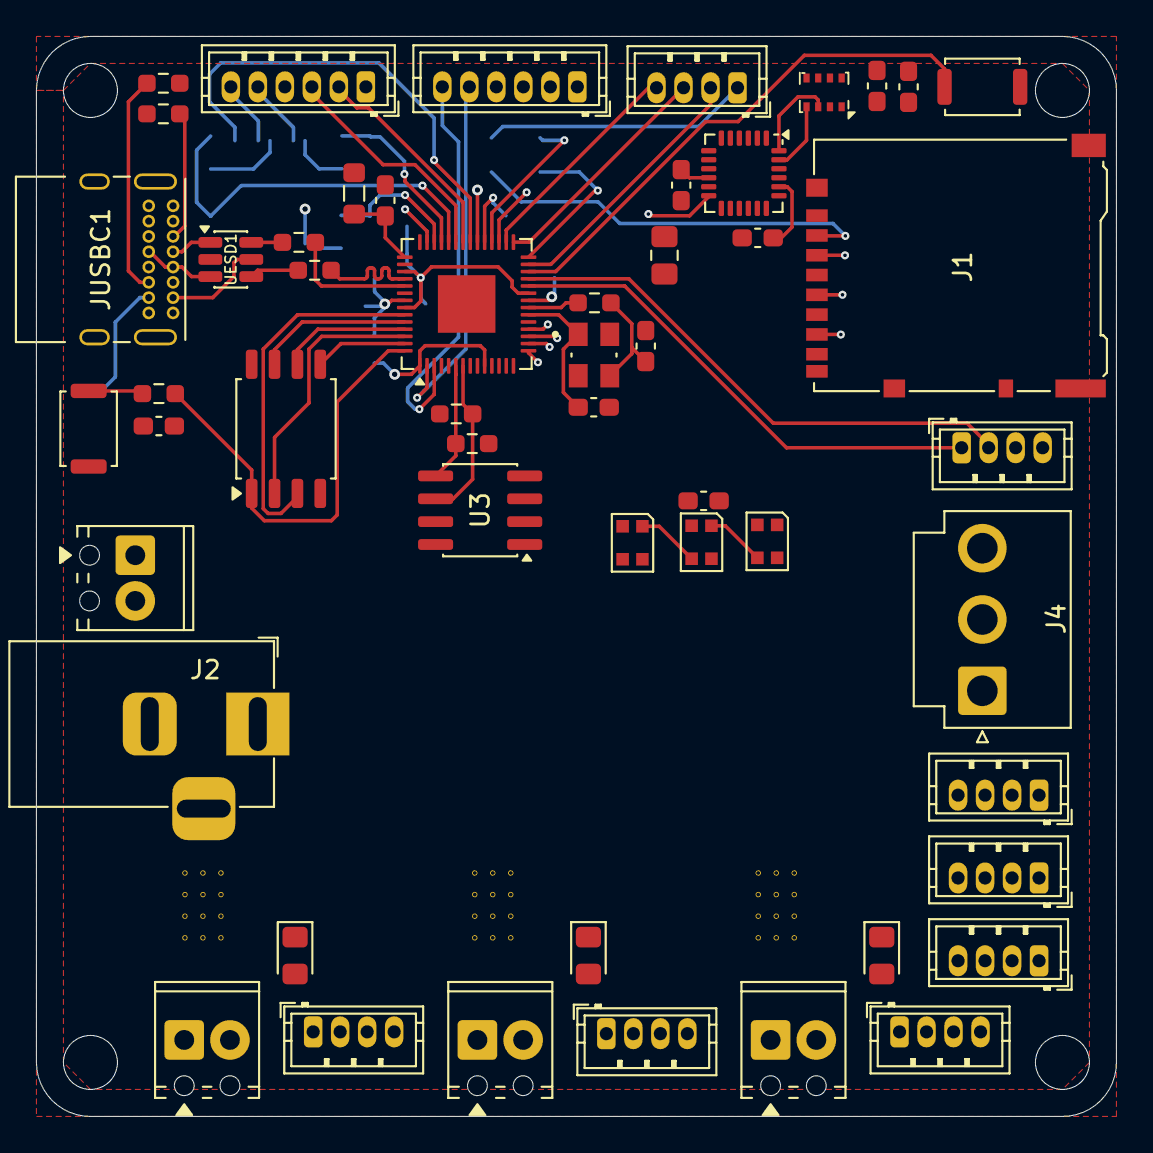
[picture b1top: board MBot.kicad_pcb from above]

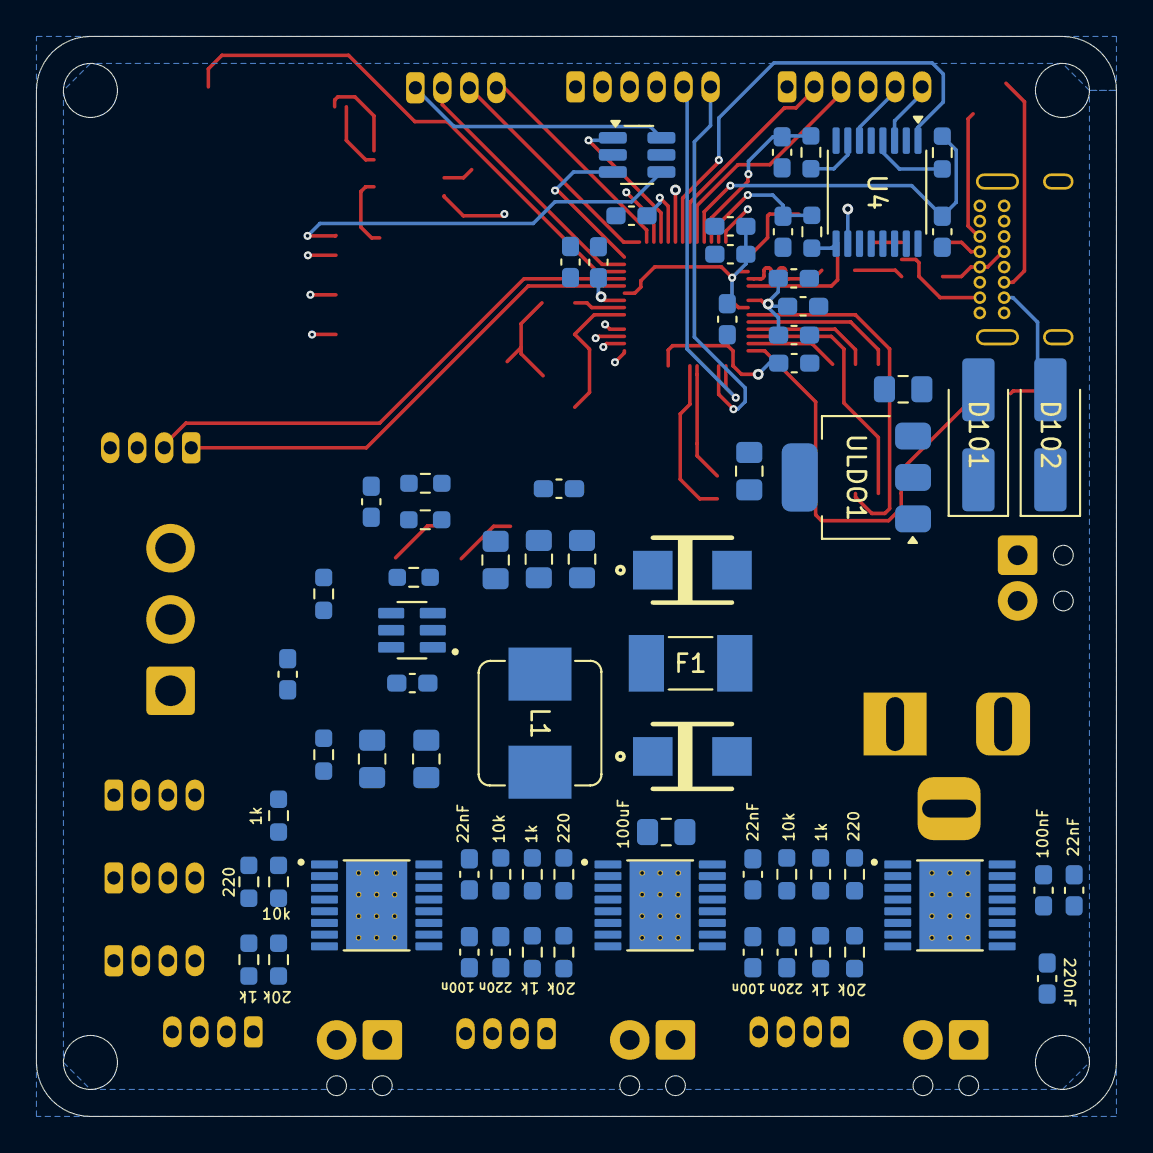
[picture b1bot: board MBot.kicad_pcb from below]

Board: 4 copper layers, 60.0 x 60.0 mm, 122 parts (70 on the bottom side), 109 nets.

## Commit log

2025-12-30 Initial Upload
2025-12-30 Add README for Astra Robotics Controller
    Added detailed documentation for the Astra Robotics Controller, including system architecture, technical specifications, pin configuration, power system, safety features, fabrication notes, and getti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
2025-12-30 Add schematic viewing instructions to README
    Added instructions to view the schematic in KiCad.
2026-03-02 Update hardware version in README
